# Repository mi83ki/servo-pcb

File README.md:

# servo-pcb

XSA2の本丸駆動用サーボ基板

## 構想設計図

構想設計図は以下になります。
モバイルバッテリー、基板、XSA2を全て回転台の上部に搭載することで、360度回転を継続できる構造とします。

## 回路ブロック図

回路ブロック図は以下になります。
赤外受発光基板をシールド基板にすることで、拡張可能とします。

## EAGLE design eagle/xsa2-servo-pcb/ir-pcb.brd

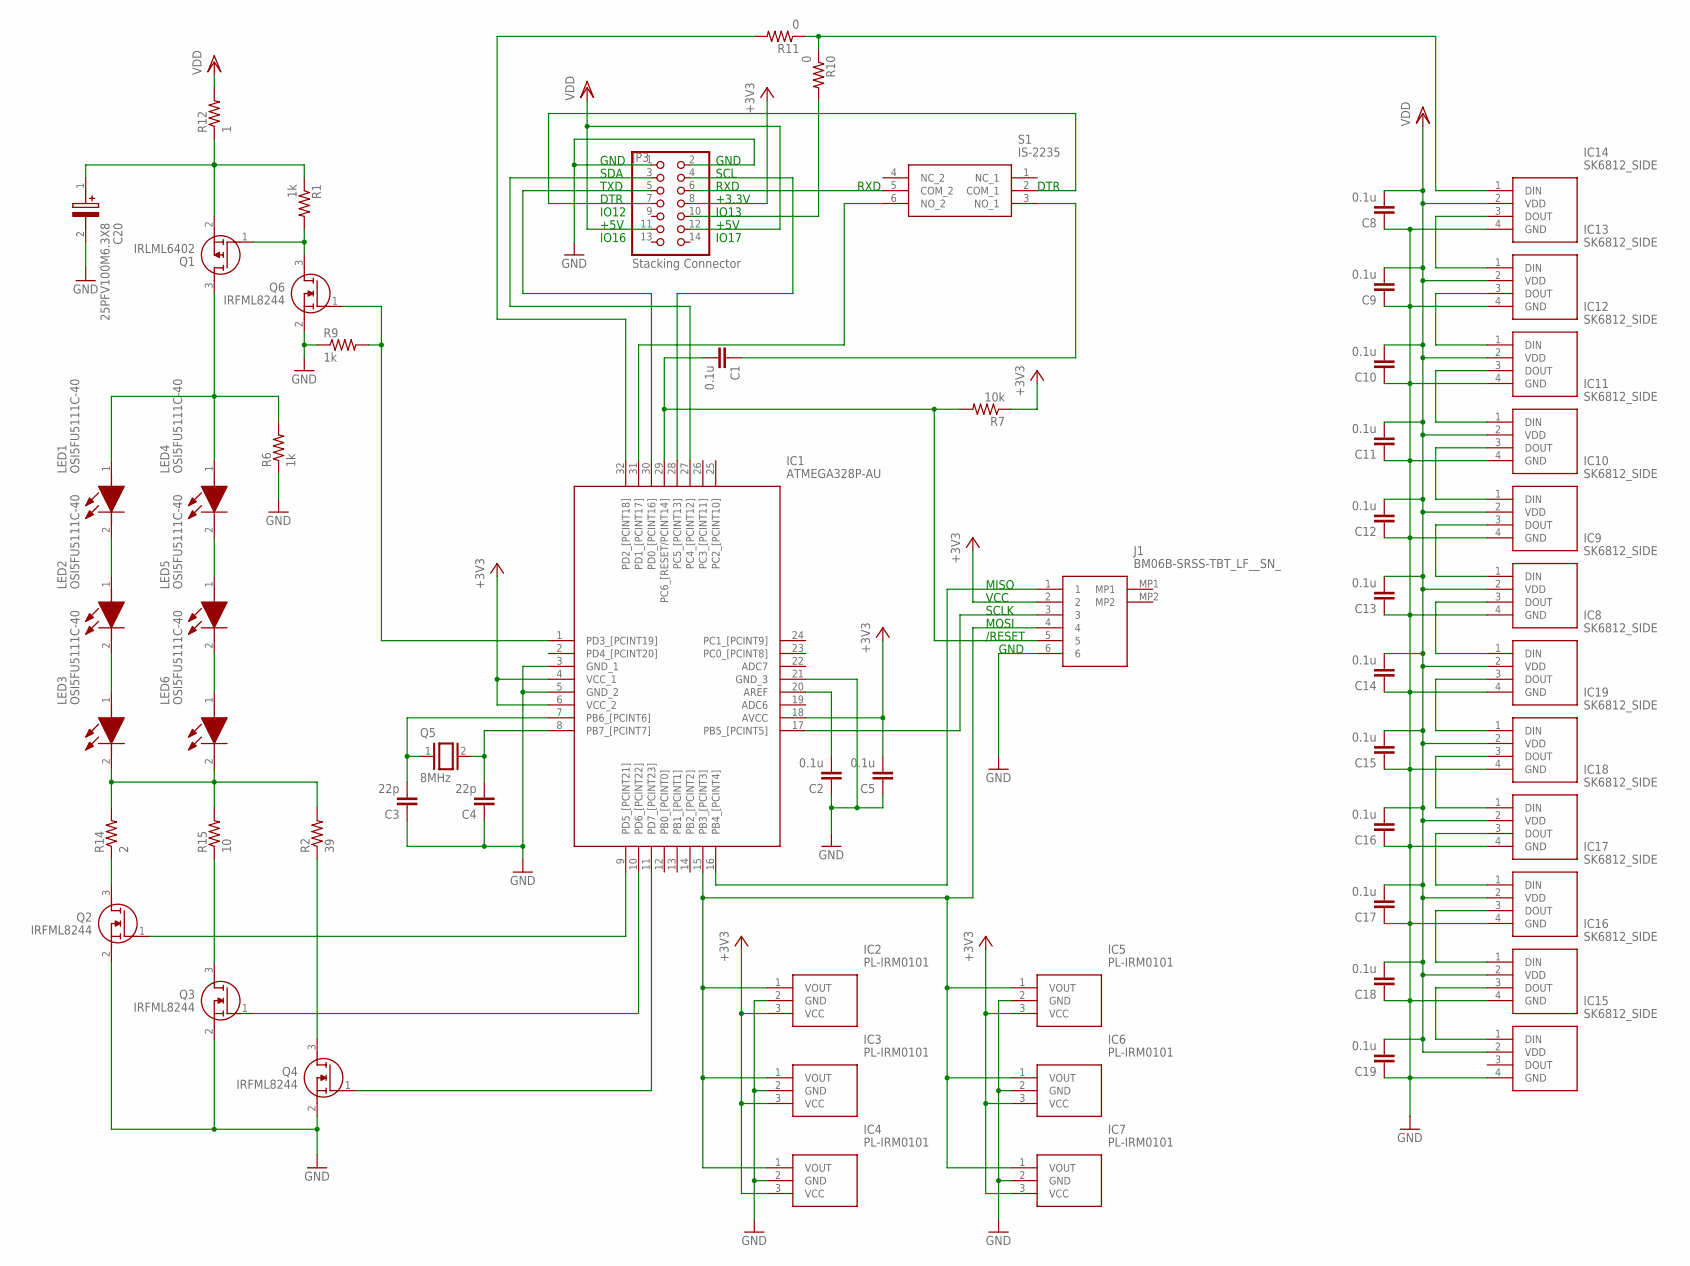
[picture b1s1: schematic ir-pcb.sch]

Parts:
C1, C2, C5, C8, C9, C10, C11, C12, C13, C14, C15, C16, C17, C18, C19: 0.1u; C0603
C3, C4: 22p; C0603
C20: 25PFV100M6.3X8; CAPAE660X800N
IC1: ATMEGA328P-AU; QFP80P900X900X120-32N
IC2, IC3, IC4, IC5, IC6, IC7: PL-IRM0101; TO254P525X740X825-3P
IC8, IC9, IC10, IC11, IC12, IC13, IC14, IC15, IC16, IC17, IC18, IC19: SK6812_SIDE; SK6812SIDE
J1: BM06B-SRSS-TBT_LF__SN_; BM06BSRSSTBTLFSN
JP3: Stacking Connector; 2X07
LED1, LED2, LED3, LED4, LED5, LED6: OSI5FU5111C-40; OSI5FU5111C40
Q1: IRLML6402; SOT95P237X112-3N
Q2, Q3, Q4, Q6: IRFML8244; SOT95P237X112-3N
Q5: 8MHz; QS
R1, R6, R9: 1k; R0603
R2: 39; R2512W
R7: 10k; R0603
R10, R11: 0; R0603
R12: 1; R2512W
R14: 2; R2512W
R15: 10; R2512W
S1: IS-2235; IS2235

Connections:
+3V3: C5.2, IC1.4 (VCC_1), IC1.6 (VCC_2), IC1.18 (AVCC), IC2.3 (VCC), IC3.3 (VCC), IC4.3 (VCC), IC5.3 (VCC), IC6.3 (VCC), IC7.3 (VCC), J1.2, JP3.8, R7.1
GND: C2.1, C3.1, C4.1, C5.1, C8.1, C9.1, C10.1, C11.1, C12.1, C13.1, C14.1, C15.1, C16.1, C17.1, C18.1, C19.1, C20.2 (-), IC1.3 (GND_1), IC1.5 (GND_2), IC1.21 (GND_3), IC2.2 (GND), IC3.2 (GND), IC4.2 (GND), IC5.2 (GND), IC6.2 (GND), IC7.2 (GND), IC8.4 (GND), IC9.4 (GND), IC10.4 (GND), IC11.4 (GND), IC12.4 (GND), IC13.4 (GND), IC14.4 (GND), IC15.4 (GND), IC16.4 (GND), IC17.4 (GND), IC18.4 (GND), IC19.4 (GND), J1.6, JP3.1, JP3.2, Q2.2 (S), Q3.2 (S), Q4.2 (S), Q6.2 (S), R6.1, R9.1
LED1: LED1.1 (A), LED4.1 (A), Q1.3 (D), R6.2
LED2: C20.1 (+), Q1.2 (S), R1.1, R12.1
LED3: LED4.2 (K), LED5.1 (A)
LED4: LED1.2 (K), LED2.1 (A)
LED5: LED5.2 (K), LED6.1 (A)
LED6: LED2.2 (K), LED3.1 (A)
LED7: LED3.2 (K), LED6.2 (K), R2.2, R14.2, R15.2
LED8: Q2.3 (D), R14.1
LED9: Q3.3 (D), R15.1
LED10: Q4.3 (D), R2.1
unnamed: IC1.16 (PB4_[PCINT4]), J1.1
unnamed: Q1.1 (G), Q6.3 (D), R1.2
unnamed: JP3.6, S1.5 (COM_2)
unnamed: IC1.17 (PB5_[PCINT5]), J1.3
unnamed: IC1.1 (PD3_[PCINT19]), Q6.1 (G), R9.2
unnamed: IC8.1 (DIN), IC9.3 (DOUT)
unnamed: C2.2, IC1.20 (AREF)
unnamed: JP3.7, S1.2 (COM_1)
unnamed: IC1.9 (PD5_[PCINT21]), Q2.1 (G)
unnamed: IC1.10 (PD6_[PCINT22]), Q3.1 (G)
unnamed: IC1.11 (PD7_[PCINT23]), Q4.1 (G)
unnamed: IC1.28 (PC5_[PCINT13]), JP3.4
unnamed: C3.2, IC1.7 (PB6_[PCINT6]), Q5.1
unnamed: IC1.30 (PD0_[PCINT16]), JP3.5
unnamed: IC13.1 (DIN), IC14.3 (DOUT)
unnamed: C1.2, IC1.29 (PC6_[RESET/PCINT14]), J1.5, R7.2
unnamed: C4.2, IC1.8 (PB7_[PCINT7]), Q5.2
unnamed: C1.1, S1.3 (NO_1)
unnamed: IC1.31 (PD1_[PCINT17]), S1.6 (NO_2)
unnamed: IC1.27 (PC4_[PCINT12]), JP3.3
unnamed: IC12.1 (DIN), IC13.3 (DOUT)
unnamed: IC11.1 (DIN), IC12.3 (DOUT)
unnamed: IC10.1 (DIN), IC11.3 (DOUT)
unnamed: IC9.1 (DIN), IC10.3 (DOUT)
unnamed: IC8.3 (DOUT), IC19.1 (DIN)
unnamed: IC18.1 (DIN), IC19.3 (DOUT)
unnamed: IC17.1 (DIN), IC18.3 (DOUT)
unnamed: IC16.1 (DIN), IC17.3 (DOUT)
unnamed: IC15.1 (DIN), IC16.3 (DOUT)
unnamed: IC1.15 (PB3_[PCINT3]), IC2.1 (VOUT), IC3.1 (VOUT), IC4.1 (VOUT), IC5.1 (VOUT), IC6.1 (VOUT), IC7.1 (VOUT), J1.4
unnamed: JP3.10, R10.2
unnamed: IC1.32 (PD2_[PCINT18]), R11.2
unnamed: IC14.1 (DIN), R10.1, R11.1
VDD: C8.2, C9.2, C10.2, C11.2, C12.2, C13.2, C14.2, C15.2, C16.2, C17.2, C18.2, C19.2, IC8.2 (VDD), IC9.2 (VDD), IC10.2 (VDD), IC11.2 (VDD), IC12.2 (VDD), IC13.2 (VDD), IC14.2 (VDD), IC15.2 (VDD), IC16.2 (VDD), IC17.2 (VDD), IC18.2 (VDD), IC19.2 (VDD), JP3.11, JP3.12, R12.2

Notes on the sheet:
GND
SDA
SCL
TXD
RXD
DTR
+3.3V
IO16
IO17
+5V
MISO
VCC
SCLK
MOSI
/RESET
IO12
IO13

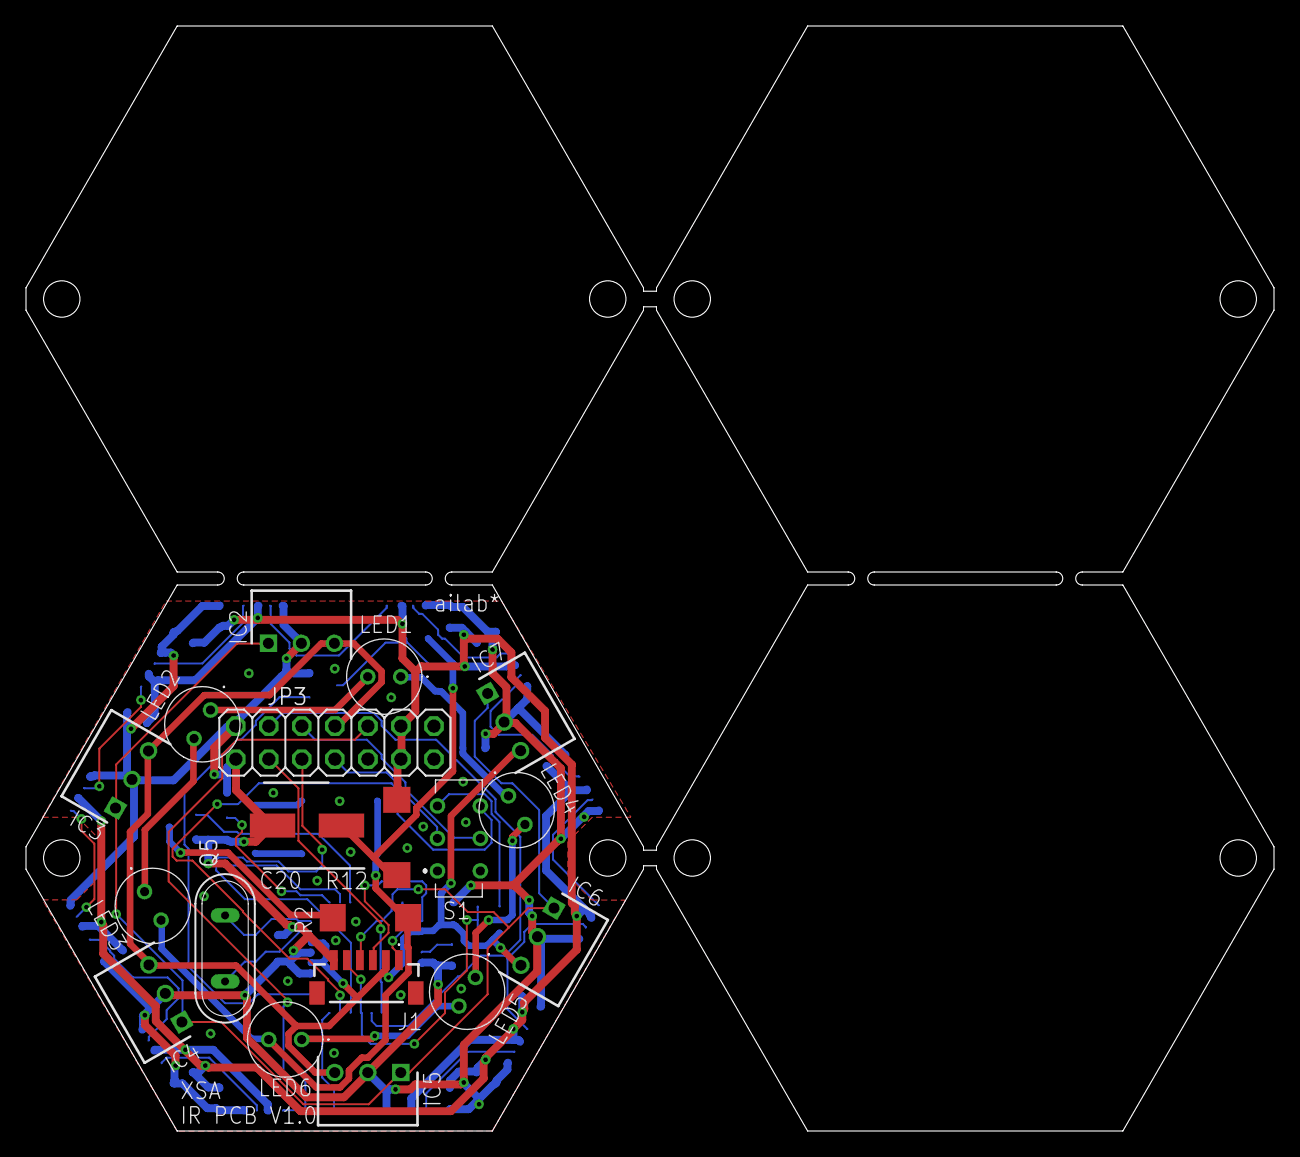
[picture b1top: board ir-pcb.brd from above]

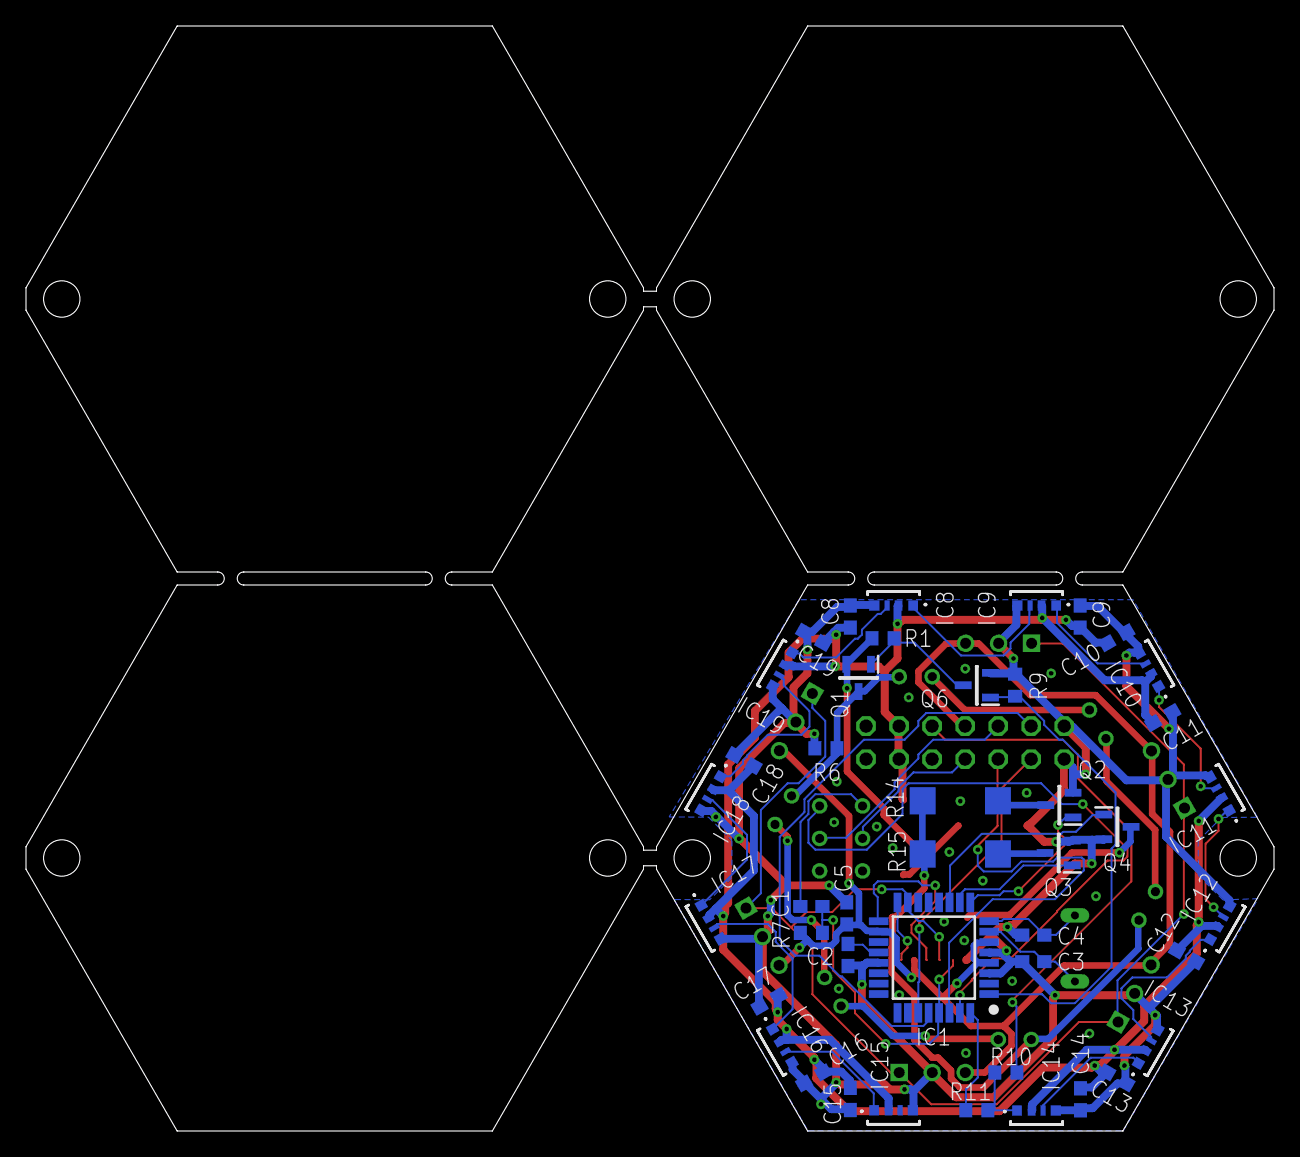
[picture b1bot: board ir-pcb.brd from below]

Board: 2 copper layers, 96.0 x 85.0 mm, 62 parts (43 on the bottom side), 46 nets.

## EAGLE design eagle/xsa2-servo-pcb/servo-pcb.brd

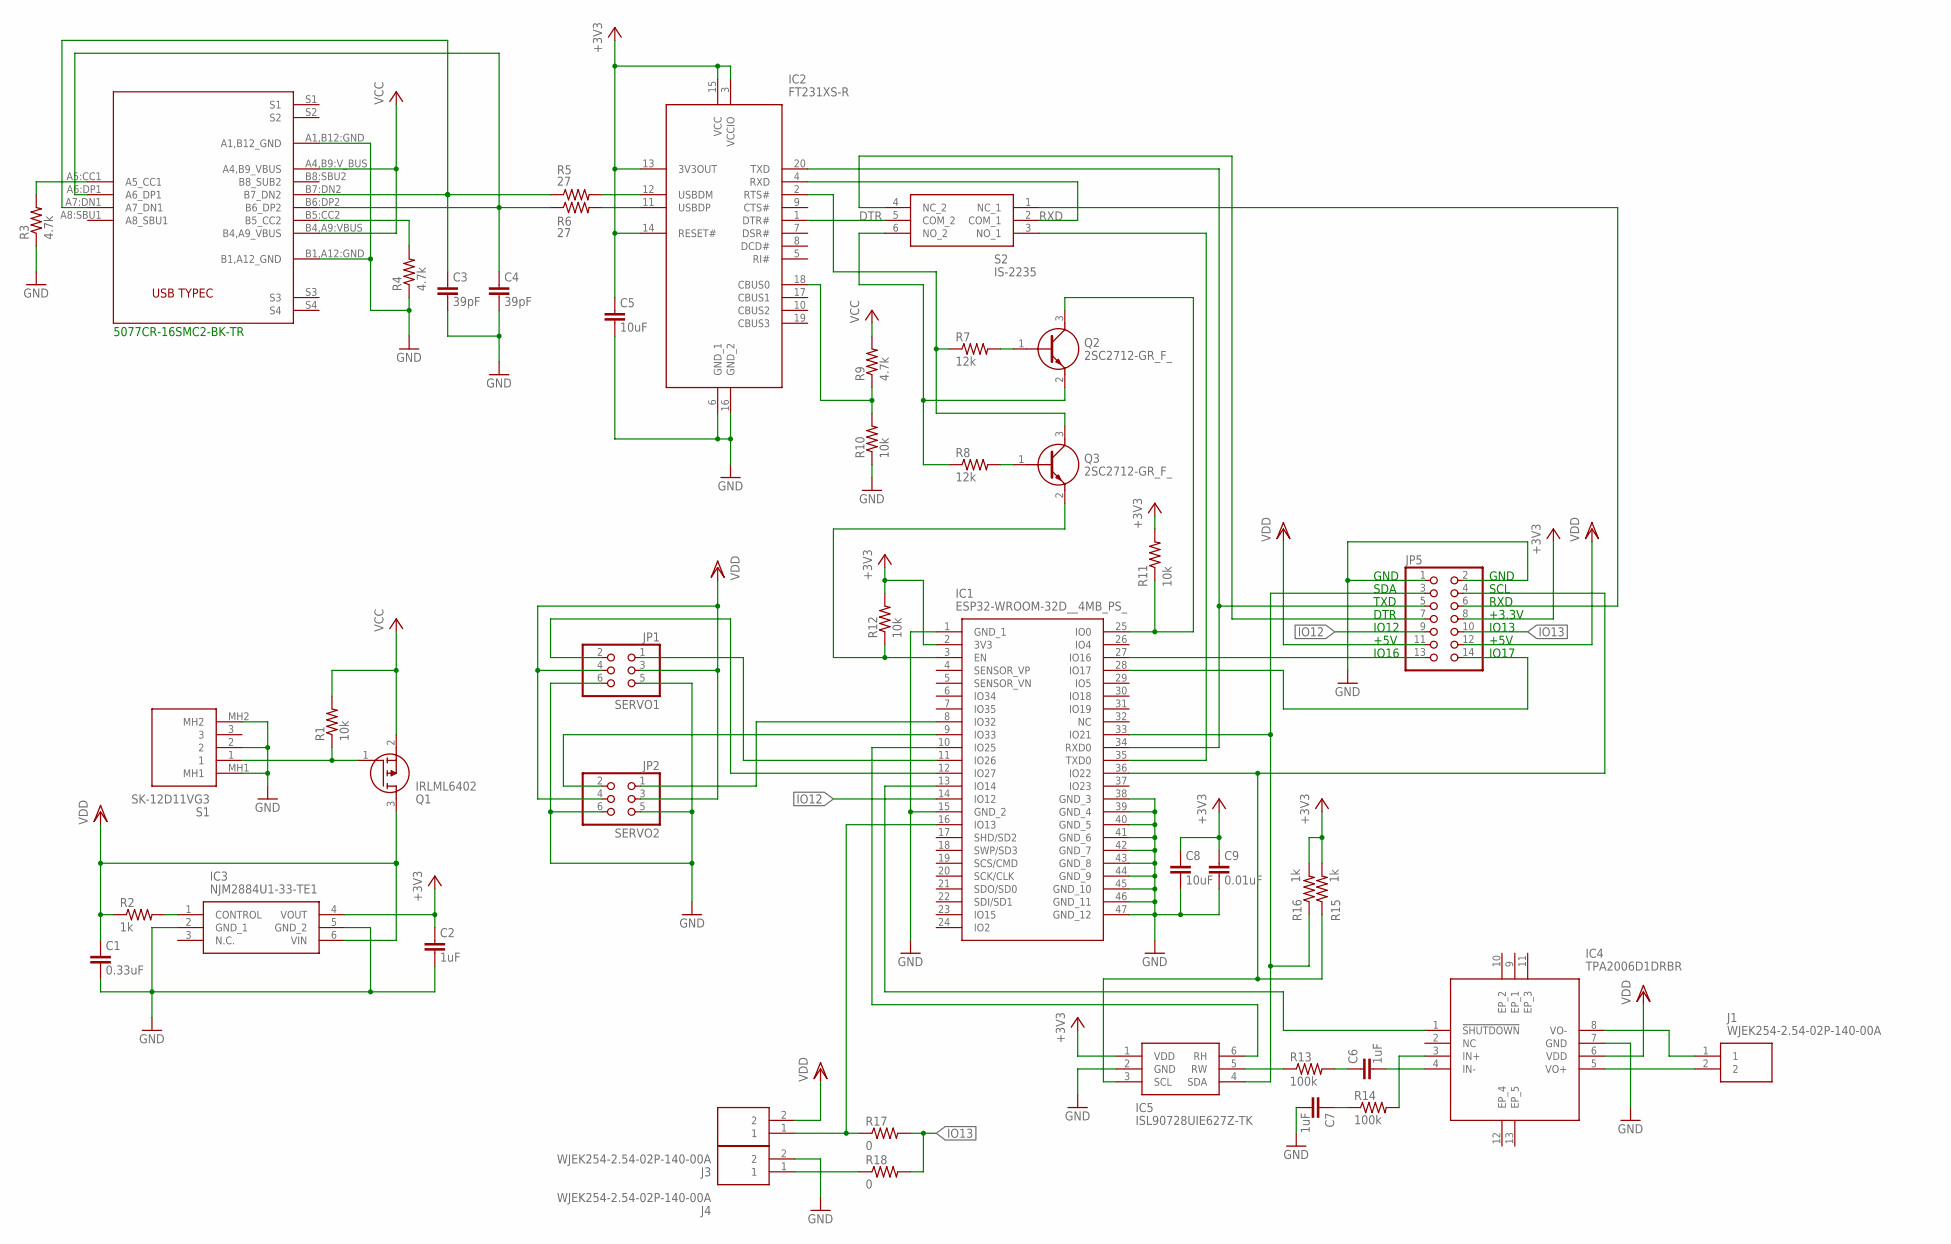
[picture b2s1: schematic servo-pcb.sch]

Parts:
C1: 0.33uF; C0603
C2, C6, C7: 1uF; C0603
C3, C4: 39pF; C0603
C5, C8: 10uF; C0805
C9: 0.01uF; C0603
IC1: ESP32-WROOM-32D__4MB_PS_; ESP32WROOM32D4MBPS
IC2: FT231XS-R; SOP64P599X175-20N
IC3: NJM2884U1-33-TE1; SOT-89-5-1
IC4: TPA2006D1DRBR
IC5: ISL90728UIE627Z-TK; SOT65P210X110-6N
J1, J3, J4: WJEK254-2.54-02P-140-00A; WJEK25425402P14000A
JP1: SERVO1; 2X03/90
JP2: SERVO2; 2X03/90
JP5: PINHD-2X7; 2X07
Q1: IRLML6402; SOT95P237X112-3N
Q2, Q3: 2SC2712-GR_F_; SSM3K7002CFULF
R1, R10, R11, R12: 10k; R0603
R2, R15, R16: 1k; R0603
R3, R4, R9: 4.7k; R0603
R5, R6: 27; R0603
R7, R8: 12k; R0603
R13, R14: 100k; R0603
R17, R18: 0; R0603
S1: SK-12D11VG3; SK12D11VG3
S2: IS-2235; IS2235
U$1: 5077CR-16-SMC2-BK-TR; 5077CR-16SMC2-BK-TR

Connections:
+3V3: C2.1, C5.1, C8.1, C9.1, IC1.2 (3V3), IC2.3 (VCCIO), IC2.13 (3V3OUT), IC2.14 (RESET#), IC2.15 (VCC), IC3.4 (VOUT), IC5.1 (VDD), JP5.8, R11.2, R12.2, R15.2, R16.2
DTR: IC2.1 (DTR#), S2.5 (COM_2)
GND: C1.2, C2.2, C3.2, C4.2, C5.2, C7.2, C8.2, C9.2, IC1.1 (GND_1), IC1.15 (GND_2), IC1.38 (GND_3), IC1.39 (GND_4), IC1.40 (GND_5), IC1.41 (GND_6), IC1.42 (GND_7), IC1.43 (GND_8), IC1.44 (GND_9), IC1.45 (GND_10), IC1.46 (GND_11), IC1.47 (GND_12), IC2.6 (GND_1), IC2.16 (GND_2), IC3.2 (GND_1), IC3.5 (GND_2), IC4.7 (GND), IC5.2 (GND), J4.2, JP1.5, JP1.6, JP2.5, JP2.6, JP5.1, JP5.2, R3.1, R4.1, R10.1, S1.2, S1.MH1, S1.MH2, U$1.A1,B12:GND (A1,B12_GND), U$1.B1,A12:GND (B1,A12_GND)
IO12: IC1.14 (IO12), JP5.9
IO13: JP5.10, R17.2, R18.2
unnamed: C4.1, R6.1, U$1.A6:DP1 (A6_DP1), U$1.B6:DP2 (B6_DP2)
unnamed: Q1.1 (G), R1.1, S1.1
unnamed: IC3.1 (CONTROL), R2.2
unnamed: IC1.28 (IO17), JP5.14
unnamed: C3.1, R5.1, U$1.A7:DN1 (A7_DN1), U$1.B7:DN2 (B7_DN2)
unnamed: IC1.34 (RXD0), IC2.20 (TXD), JP5.5
unnamed: IC2.12 (USBDM), R5.2
unnamed: IC2.11 (USBDP), R6.2
unnamed: IC2.2 (RTS#), Q3.3 (C), R7.1
unnamed: Q2.1 (B), R7.2
unnamed: Q2.2 (E), R8.1, S2.6 (NO_2)
unnamed: Q3.1 (B), R8.2
unnamed: IC2.18 (CBUS0), R9.1, R10.2
unnamed: IC1.3 (EN), Q3.2 (E), R12.1
unnamed: IC1.25 (IO0), Q2.3 (C), R11.1
unnamed: IC1.35 (TXD0), S2.3 (NO_1)
unnamed: JP5.7, S2.4 (NC_2)
unnamed: IC5.5 (RW), R13.1
unnamed: C6.1, R13.2
unnamed: C6.2, IC4.4 (IN-)
unnamed: IC4.3 (IN+), R14.2
unnamed: C7.1, R14.1
unnamed: IC1.36 (IO22), IC5.3 (SCL), JP5.4, R15.1
unnamed: IC1.33 (IO21), IC5.4 (SDA), JP5.3, R16.1
unnamed: IC1.13 (IO14), IC4.1 (!SHUTDOWN)
unnamed: IC4.8 (VO-), J1.1
unnamed: IC4.5 (VO+), J1.2
unnamed: IC1.10 (IO25), IC5.6 (RH)
unnamed: IC1.16 (IO13), J3.1, R17.1
unnamed: IC1.11 (IO26), JP1.1
unnamed: IC1.12 (IO27), JP1.2
unnamed: IC1.8 (IO32), JP2.1
unnamed: IC1.9 (IO33), JP2.2
unnamed: IC1.27 (IO16), JP5.13
unnamed: R4.2, U$1.B5:CC2 (B5_CC2)
unnamed: J4.1, R18.1
unnamed: JP5.6, S2.1 (NC_1)
unnamed: R3.2, U$1.A5:CC1 (A5_CC1)
RXD: IC2.4 (RXD), S2.2 (COM_1)
VCC: Q1.2 (S), R1.2, R9.2, U$1.A4,B9:V_BUS (A4,B9_VBUS), U$1.B4,A9:VBUS (B4,A9_VBUS)
VDD: C1.1, IC3.6 (VIN), IC4.6 (VDD), J3.2, JP1.3, JP1.4, JP2.3, JP2.4, JP5.11, JP5.12, Q1.3 (D), R2.1

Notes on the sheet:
RXD
TXD
DTR
SDA
SCL
IO16
IO17
IO13
IO12
+5V
GND
5077CR-16SMC2-BK-TR
+3.3V

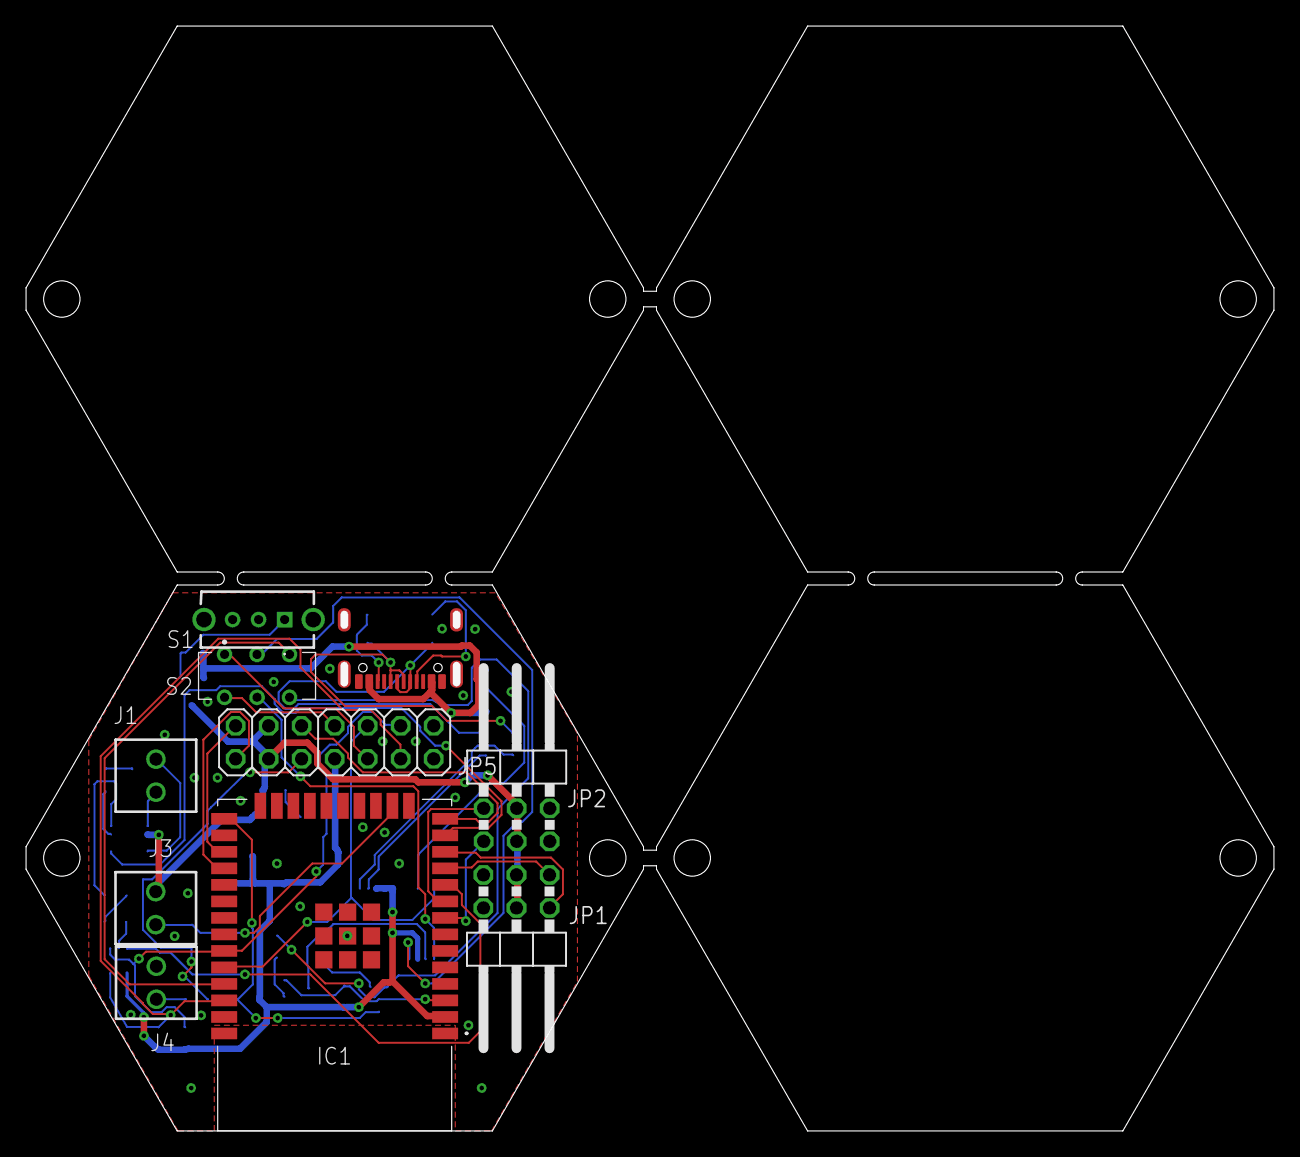
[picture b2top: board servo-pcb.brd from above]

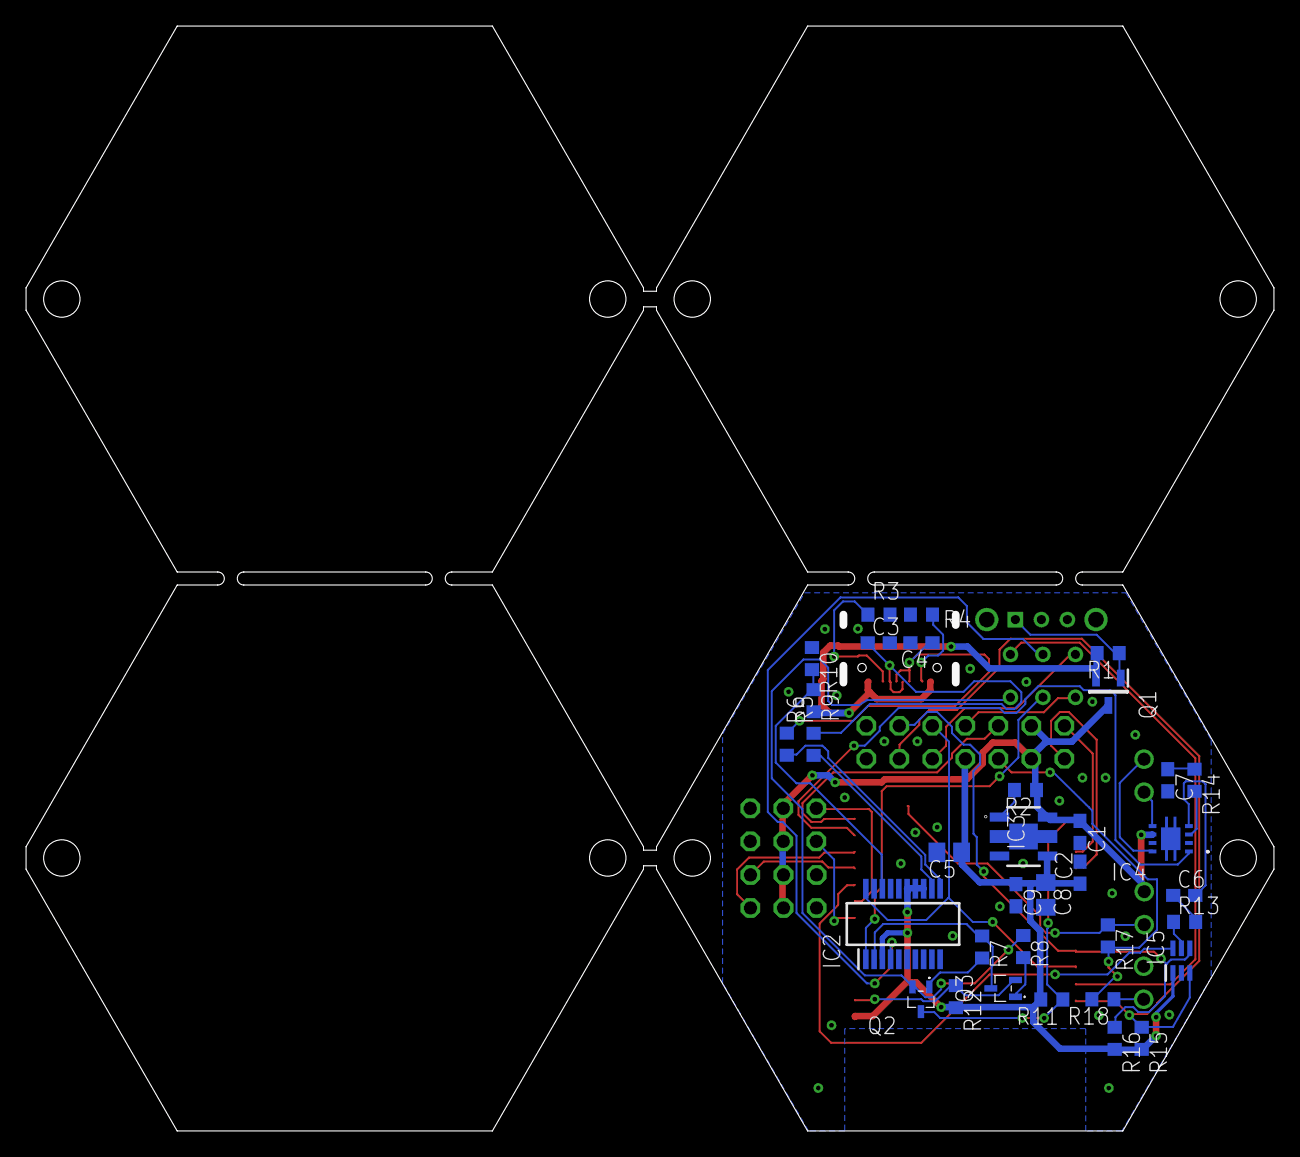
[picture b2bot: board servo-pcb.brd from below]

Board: 2 copper layers, 95.4 x 84.4 mm, 44 parts (34 on the bottom side), 46 nets.

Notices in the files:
parts and their libraries:
FaBo-Connetor: Released under the Creative Commons Attribution-ShareAlike 4.0 License
https://creativecommons.org/licenses/by-sa/4.0
